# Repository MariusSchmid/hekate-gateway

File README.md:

# hekate
Outdoor Lora Gateway with Pico Pi.

Full Documentation: [readthedocs]( https://hekate-gateway.readthedocs.io/en/latest/)

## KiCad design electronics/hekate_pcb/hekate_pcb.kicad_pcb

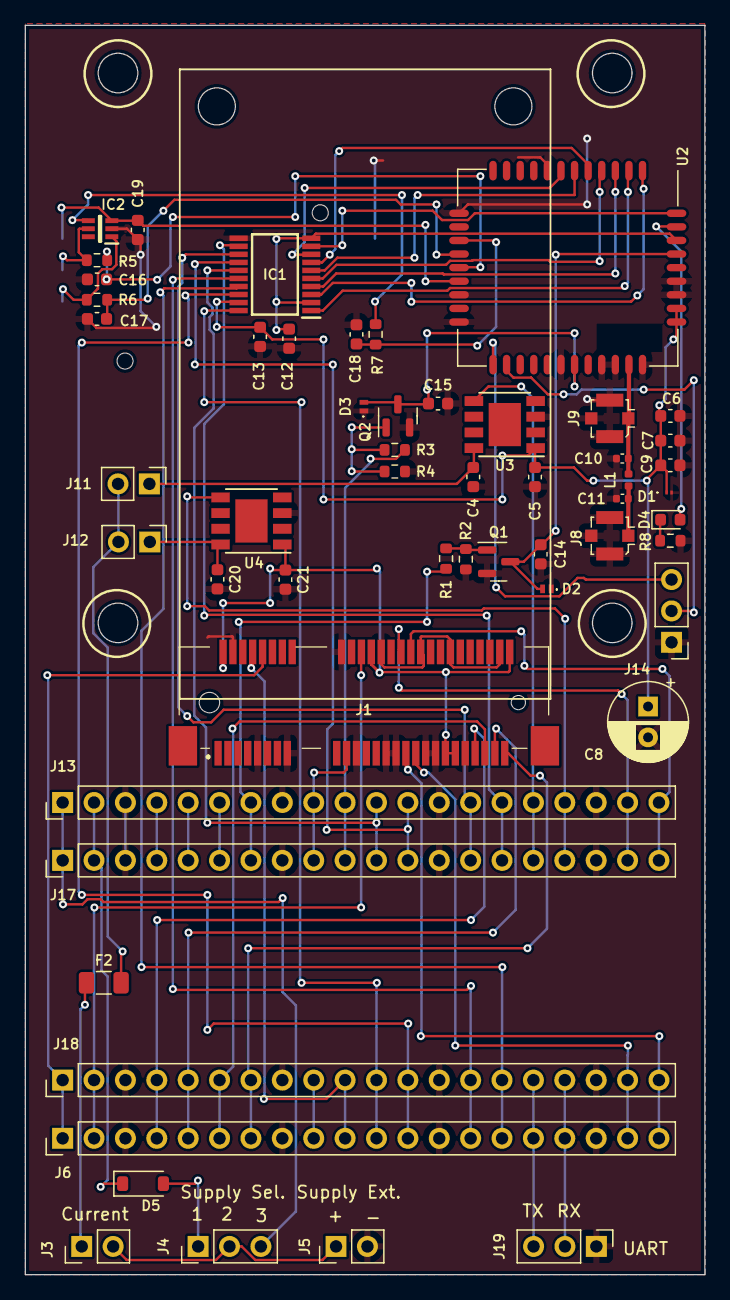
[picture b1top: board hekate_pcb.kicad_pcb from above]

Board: 2 copper layers, 55.0 x 101.1 mm, 55 parts (1 on the bottom side), 67 nets.

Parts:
C4, C5, C20, C21: 4.7µF; C_0603_1608Metric
C6, C12, C13, C14, C15, C19: 100nF; C_0603_1608Metric
C7: 1µF; C_0603_1608Metric
C8: 470 µF; CP_Radial_D6.3mm_P2.50mm
C9: 10µF; C_0603_1608Metric
C10, C11: C; C_0402_1005Metric
C16, C17, C18: 22pF; C_0603_1608Metric
D1: DF2S5.1ASL,L3F; DF2S51ASLL3F
D2, D3: PESD3V3S1BLYL; PESD5V0S1BL315
D4: LED; LED_0603_1608Metric
D5: D_Schottky; D_SOD-123
F2: Fuse; Fuse_1206_3216Metric
IC1: TXB0108PWR; SOP65P640X120-20N
IC2: SMF05CT1G; SOT65P210X110-6N
J1: 1775862-2; 17758622
J3: Current; PinHeader_1x02_P2.54mm_Vertical
J4: SUPPLY_SELECT; PinHeader_1x03_P2.54mm_Vertical
J5: EXT_SUPPLY; PinHeader_1x02_P2.54mm_Vertical
J6, J13, J17, J18: Conn_01x20; PinHeader_1x20_P2.54mm_Vertical
J8, J9: Conn_Coaxial; U.FL_Molex_MCRF_73412-0110_Vertical
J10: 7111S2015X02LF
J11: SIM Current; PinHeader_1x02_P2.54mm_Vertical
J12: Lora Current; PinHeader_1x02_P2.54mm_Vertical
J14: SIM_UART2; PinHeader_1x03_P2.54mm_Vertical
J19: UART_DEBUG; PinHeader_1x03_P2.54mm_Vertical
L1: L; L_0402_1005Metric
Q1, Q2: BC817; SOT-23
R1, R3: 4.7K; R_0603_1608Metric
R2, R4: 47K; R_0603_1608Metric
R5, R6, R7: 22R; R_0603_1608Metric
R8: 56 R; R_0603_1608Metric
U2: SIM7020E; SIMCom_SIM800C
U3, U4: AP7361C-33SPR-13; Diodes_SO-8EP

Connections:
3V3_EN: J13.4, J17.4
3V3_OUT: J13.5, J17.5
+VSUP: F2.2, J11.2, J12.2
ADC_VREF: J13.6, J17.6
GND: C4.2, C5.2, C6.2, C7.2, C8.2, C9.2, C10.2, C11.2, C12.2, C13.1, C14.2, C15.2, C16.2, C17.2, C18.2, C19.2, C20.2, C21.2, D1.2 (A), D2.1 (K1), D3.1 (K1), IC1.11 (GND), IC2.2 (A), J1.4 (GND_1), J1.9 (GND_2), J1.15 (GND_3), J1.18 (GND_4), J1.21 (GND_5), J1.26 (GND_6), J1.27 (GND_7), J1.29 (GND_8), J1.34 (GND_9), J1.35 (GND_10), J1.37 (GND_11), J1.40 (GND_12), J1.43 (GND_13), J1.50 (GND_14), J5.2, J6.3, J6.8, J6.13, J6.18, J8.2 (Ext), J9.2 (Ext), J10.5, J13.3, J13.8, J13.13, J13.18, J14.1, J17.3, J17.8, J17.13, J17.18, J18.3, J18.8, J18.13, J18.18, J19.1, Q1.2 (E), Q2.2 (E), R2.2, R4.2, R8.1, U2.8 (GND), U2.13 (GND), U2.19 (GND), U2.21 (GND), U2.27 (GND), U2.30 (GND), U2.31 (GND), U2.33 (GND), U2.36 (GND), U2.37 (GND), U3.3 (GND), U4.3 (GND)
LORA_1PPS: J1.19 (RESERVED(UIM_C4), J13.9, J17.9
LORA_EN: J13.17, J17.17, U4.5 (EN)
LORA_I2C_SCL: J1.30 (SMB_CLK), J13.19, J17.19
LORA_I2C_SDA: J1.32 (SMB_DATA), J13.20, J17.20
LORA_SPI_CLK: J1.45 (RESERVED_1), J6.4, J18.4
LORA_SPI_MISO: J1.47 (RESERVED_2), J6.6, J18.6
LORA_SPI_MOSI: J1.49 (RESERVED_3), J6.5, J18.5
LORA_SX1262_BUSY: J1.8 (UIM_PWR), J6.10, J18.10
LORA_SX1262_IO1: J1.33 (PETP0), J6.19, J18.19
LORA_SX1262_IO2: J1.31 (PETN0), J6.20, J18.20
LORA_SX1262_RESET: J1.10 (UIM_DATA), J6.1, J18.1
LORA_SX1302_CSN: J1.51 (RESERVED_4), J6.7, J18.7
LORA_SX1302_RESET: J1.22 (PERST#), J6.2, J18.2
unnamed: C14.1, D2.2 (K2), Q1.3 (C), U2.39 (~PWRKEY)
unnamed: C15.1, D3.2 (K2), Q2.3 (C), U2.28 (~RESET)
unnamed: D4.1 (K), R8.2
unnamed: D5.2 (A), J4.1
unnamed: D5.1 (K), J13.2, J17.2
unnamed: IC2.1 (K_1), J10.3, R6.2
unnamed: IC2.4 (K_3), J10.7, R7.1
unnamed: IC2.5 (K_4), J10.2, R5.2
unnamed: F2.1, J3.1
unnamed: J3.2, J4.2, J5.1
unnamed: C11.1, J8.1 (In), L1.2
unnamed: C10.1, J9.1 (In), L1.1, U2.32 (ANT)
unnamed: C4.1, J11.1, U3.8 (IN)
unnamed: C20.1, J12.1, U4.8 (IN)
unnamed: J4.3, J13.1, J17.1
unnamed: J6.9, J18.9
unnamed: Q1.1 (B), R1.2, R2.1
unnamed: Q2.1 (B), R3.2, R4.1
SIM_CARD_CLK: C17.1, R6.1, U2.16 (SIM_CLK)
SIM_CARD_DATA: C18.1, R7.2, U2.15 (SIM_DATA)
SIM_CARD_RST: C16.1, R5.1, U2.17 (SIM_RST)
SIM_CARD_VCC: C19.1, IC2.3 (K_2), J10.1, U2.18 (SIM_VDD)
SIM_EN: J13.16, J17.16, U3.5 (EN)
SIM_NETLIGHT: D4.2 (A), U2.41 (NETLIGHT)
SIM_PWR_KEY: J13.7, J17.7, R1.1
SIM_RESET: J13.10, J17.10, R3.1
SIM_STATUS: IC1.9 (A8), U2.42 (STATUS)
SIM_STATUS_3_3V: IC1.12 (B8), J13.15, J17.15
SIM_UART1_CTS: IC1.5 (A4), U2.4 (UART1_CTS)
SIM_UART1_CTS_3_3V: IC1.16 (B4), J6.14, J18.14
SIM_UART1_DCD: IC1.7 (A6), U2.5 (UART1_DCD)
SIM_UART1_DCD_3_3V: IC1.14 (B6), J13.12, J17.12
SIM_UART1_DTR: IC1.6 (A5), U2.6 (UART1_DTR)
SIM_UART1_DTR_3_3V: IC1.15 (B5), J13.11, J17.11
SIM_UART1_RI: IC1.8 (A7), U2.7 (UART1_RI)
SIM_UART1_RI_3_3V: IC1.13 (B7), J13.14, J17.14
SIM_UART1_RTS: IC1.4 (A3), U2.3 (UART1_RTS)
SIM_UART1_RTS_3_3V: IC1.17 (B3), J6.15, J18.15
SIM_UART1_RXD: IC1.1 (A1), U2.2 (UART1_RXD)
SIM_UART1_RXD_3_3V: IC1.20 (B1), J6.11, J18.11
SIM_UART1_TXD: IC1.3 (A2), U2.1 (UART1_TXD)
SIM_UART1_TXD_3_3V: IC1.18 (B2), J6.12, J18.12
SIM_UART2_RXD: J14.2, U2.23 (UART2_RXD)
SIM_UART2_TXD: J14.3, U2.22 (UART2_TXD)
SIM_VDD: C5.1, C6.1, C7.1, C8.1, C9.1, C13.2, D1.1 (K), IC1.19 (VCCB), U2.34 (VBAT), U2.35 (VBAT), U3.1 (OUT)
SIM_VDD_EXT: C12.1, IC1.2 (VCCA), IC1.10 (OE), U2.40 (VDD_EXT)
USART_DEBUG_RX: J6.17, J18.17, J19.2
USART_DEBUG_TX: J6.16, J18.16, J19.3
gateway_3V3: C21.1, J1.2 (3.3VAUX), J1.24 (+3.3VAUX_1), J1.39 (+3.3VAUX_2), J1.41 (+3.3VAUX_3), J1.52 (+3.3VAUX_4), U4.1 (OUT)

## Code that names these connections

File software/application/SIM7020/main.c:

#include "pico/stdlib.h"

#include <stdio.h>
#include <time.h>
#include <sys/time.h>

#include "hardware/uart.h"
#include "hardware/irq.h"

#include "tusb.h"

#include "log.h"

#define UART_ID uart1
#define UART_TX_PIN 8
#define UART_RX_PIN 9

#define BAUD_RATE 115200
#define DATA_BITS 8
#define STOP_BITS 1
#define PARITY UART_PARITY_NONE

#define SIM_PWR_PIN 28
#define SIM_EN_PIN 19
#define SIM_RESET_PIN 26

#define WAIT_FOR_CDC 0

static bool uart_received = false;
static bool uart_cnt = 0;
// static char uart_response[1024];

// RX interrupt handler
void on_uart_rx()
{

    while (uart_is_readable(UART_ID))
    {
        uint8_t ch = uart_getc(UART_ID);
        printf("%c", ch);
    }
}

static void my_uart_init()
{

    uart_init(UART_ID, BAUD_RATE);
    gpio_set_function(UART_TX_PIN, GPIO_FUNC_UART);
    gpio_set_function(UART_RX_PIN, GPIO_FUNC_UART);
    int __unused actual = uart_set_baudrate(UART_ID, BAUD_RATE);

    // Set UART flow control CTS/RTS, we don't want these, so turn them off
    uart_set_hw_flow(UART_ID, false, false);

    // Set our data format
    uart_set_format(UART_ID, DATA_BITS, STOP_BITS, PARITY);

    // Turn off FIFO's - we want to do this character by character
    uart_set_fifo_enabled(UART_ID, false);

    // Set up a RX interrupt
    // We need to set up the handler first
    // Select correct interrupt for the UART we are using
    int UART_IRQ = UART_ID == uart0 ? UART0_IRQ : UART1_IRQ;

    // And set up and enable the interrupt handlers
    irq_set_exclusive_handler(UART_IRQ, on_uart_rx);
    irq_set_enabled(UART_IRQ, true);

    // Now enable the UART to send interrupts - RX only
    uart_set_irq_enables(UART_ID, true, false);
}

static void set_apn()
{
    uart_puts(UART_ID, "AT+CFUN=0\r\n");
    sleep_ms(10000);
    uart_puts(UART_ID, "AT*MCGDEFCONT=\"IP\",\"iot.1nce.net\"\r\n");
    sleep_ms(1000);
    uart_puts(UART_ID, "AT+CFUN=1\r\n");
    sleep_ms(10000);
}

static void ntp_example()
{
    uart_puts(UART_ID, "AT\r\n");
    sleep_ms(1000);
    uart_puts(UART_ID, "AT+CMEE=2\r\n"); // extebded error report
    sleep_ms(1000);
    uart_puts(UART_ID, "AT+CPIN?\r\n");
    sleep_ms(1000);
    set_apn();
    uart_puts(UART_ID, "AT+CGCONTRDP\r\n");
    sleep_ms(5000);

#if CHINESE_NTP == 1
    uart_puts(UART_ID, "AT+CSNTPSTART=\"jp.ntp.org.cn\",\"+32\"\r\n");
#else
    uart_puts(UART_ID, "AT+CSNTPSTART=\"pool.ntp.org\",\"+48\"\r\n");
#endif
    sleep_ms(20000);
    uart_puts(UART_ID, "AT+CCLK?\r\n");
    sleep_ms(5000);
    uart_puts(UART_ID, "AT+CSNTPSTOP\r\n");
    sleep_ms(5000);
}

static void send_udp(){

}

int main()
{

#if 1
    if (!stdio_init_all())
    {
        log_error("failed: stdio_usb_init()");
    }
#endif
#if (WAIT_FOR_CDC == 1)
    while (!tud_cdc_connected())
    {
        printf(".");
        sleep_ms(500);
    }
#endif


    my_uart_init();
    log_info("staart");
    const uint sim_pwr_key = SIM_PWR_PIN;
    const uint sim_en_key = SIM_EN_PIN;
    const uint sim_reset_key = SIM_RESET_PIN;

    // Initialize LoRa enable pin
    gpio_init(sim_pwr_key);
    gpio_init(sim_en_key);
    gpio_init(sim_reset_key);

    gpio_set_dir(sim_pwr_key, GPIO_OUT);
    gpio_set_dir(sim_en_key, GPIO_OUT);
    gpio_set_dir(sim_reset_key, GPIO_OUT);

    gpio_put(sim_reset_key, false); // no reset
    gpio_put(sim_pwr_key, true);    // power key down

    sleep_ms(100);
    gpio_put(sim_en_key, true);
    sleep_ms(100);

    gpio_put(sim_pwr_key, false); // release power key
    sleep_ms(100);

    // gpio_put(sim_reset_key, false);
    // sleep_ms(100);
    // gpio_put(sim_reset_key, false);
    // sleep_ms(100);
    gpio_put(sim_pwr_key, true); // press power key
    sleep_ms(2000);
    gpio_put(sim_pwr_key, false); // release power key
    sleep_ms(100);

    ntp_example();
    while (true)
    {
        // uart_puts(UART_ID, "AT\r\n");
        sleep_ms(1000);
        // log_info("ok");
        // sleep_ms(500);
    }
}

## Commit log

2024-02-04 added submodule basicstation
2024-02-04 added config and keys for simulation
2024-02-05 can build station for linux with wsl
2024-02-05 mbedtls disable testing and programs
2024-02-05 cleaned up cmake
2024-02-05 cmake policy for options
2024-02-07 added root cmake, cleaned up key files
2024-02-07 put linux in paranthesis, example is working
2024-02-07 ignore not needed key files
2024-02-07 use micropython 1.22.1
2024-02-08 moved source files to the lib folder
2024-02-08 added lgw folder, can build again, override cmake default settings
2024-02-10 added src folder and include folder for hekatelib
2024-02-10 can compile hekate module
2024-02-10 can build for unix and rp2
2024-02-10 new line stuff etc
2024-02-11 can build for my, unix same time is not supported
2024-02-11 can build for unix port
2024-02-11 started with the hal for hekate
2024-02-11 can build for rp2
2024-02-12 Fix CRLF
2024-02-12 added redthedocs
2024-02-12 added read the docs yaml
2024-02-12 moved the readthedocs yml into docs
2024-02-12 added example pyproject
2024-02-12 doc: improved the titel underline
2024-03-03 added papyrus
2024-03-03 continued witch system architecture
2024-03-03 added drawio
2024-03-03 added md architecture
2024-03-03 disable drawio
2024-03-03 added css for objectives
2024-05-30 doc: added base architecture
2024-05-31 doc: can generate objective table
2024-05-31 doc: create path for generated md file in case not exist
2024-05-31 doc: added generated documents to toc
2024-06-24 added electronics
2024-06-24 script to generate risks
2024-06-24 added risks to architecture
2024-06-24 upper PNG in documentation
2024-06-24 added base architecture context
2024-07-09 doc: added hw overview
2024-07-09 remove example lumache
2024-07-09 move software into software folder
2024-07-11 remove basic station
2024-07-11 remove ttn config stuff
2024-07-11 remove hekatelib
2024-07-11 remove the external libraries
2024-07-12 added concentrator
2024-07-12 moved micropython to version 1.23
2024-07-12 added example mpy module
2024-07-12 added readme and runmpy script
2024-07-12 update gitignore and vscode folder
2024-07-12 update docs
2024-07-12 added devcontianer config
2024-07-12 added micropython patch
2024-07-12 added extensions to dev container
2024-07-14 raspi debug possible
2024-07-14 git config in dockerfile
2024-07-14 can start concentrator
2024-07-14 can receive messages with concentrator
2024-07-14 can connect udp wifi
2024-07-14 submodules for rp2 sdk
2024-07-15 dockerfile: fix pico-sdk path
2024-07-15 serial uart with usb is working
2024-07-15 can send status to ttn network
2024-07-15 cleanup
2024-07-16 packet forwarder task is working
2024-07-16 gateway task can run
2024-07-19 packet converting for semtech protocol is working
2024-07-19 ntp server is working
2024-07-19 rxpkt is working
2024-07-20 bat scripts for simpler development
2024-07-20 set git global safe
2024-07-20 use log functionality for forwareder task and concentrator
2024-07-20 application for sim7020e
2024-07-20 ntp with sim7020 and freertos working
2024-07-20 sim task is setting time
2024-07-21 start to split wifi and sim
2024-07-21 ssid and pwd in devcontainer
2024-07-21 changed folder structure
2024-07-21 restructure with internet_if
2024-07-22 wifi is working again with restructuring
2024-07-22 start to use static memory tasks
2024-07-22 task memory statistics
2024-07-22 udp sending with lte is working
2024-07-22 rename gateway task to lora task
2024-07-22 doc: added sim state machine
2024-07-24 moved sim7020 uart into separate folder
2024-07-28 sim7020 is working with state machine
2024-07-28 forwarder with wifi is working again
2024-07-29 can get sim state info
2024-07-30 prepare status task for sim information, not working so far
2024-07-30 move timing into config file
2024-08-01 print only state changes
